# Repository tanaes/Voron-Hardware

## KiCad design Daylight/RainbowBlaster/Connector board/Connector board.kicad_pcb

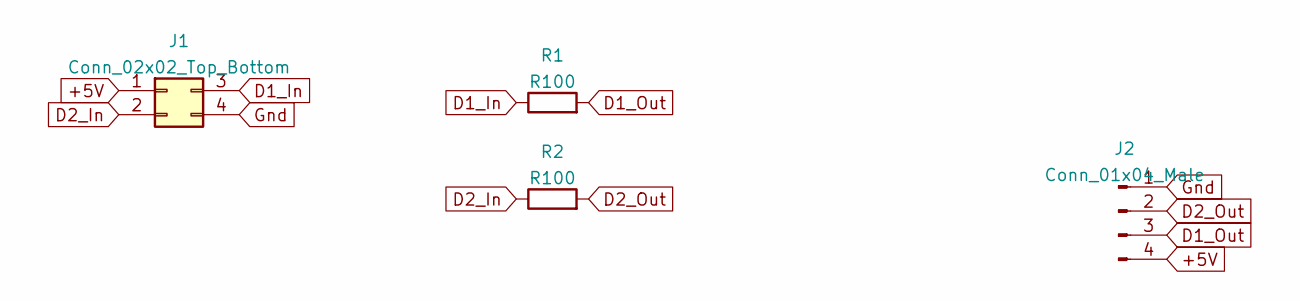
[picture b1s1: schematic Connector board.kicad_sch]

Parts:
J1: Conn_02x02_Top_Bottom; Molex_Micro-Fit_3.0_43045-0400_2x02_P3.00mm_Horizontal
J2: Conn_01x04_Male; PinHeader_1x04_P2.54mm_Vertical
R1, R2: R100; R_0805_2012Metric

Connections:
+5V: J1.1, J2.4
D1_In: J1.3, R1.1
D1_Out: J2.3, R1.2
D2_In: J1.2, R2.1
D2_Out: J2.2, R2.2
Gnd: J1.4, J2.1

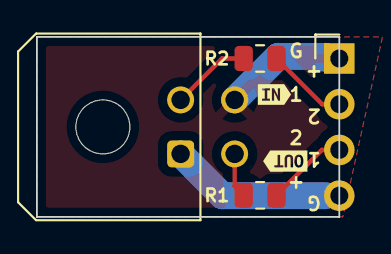
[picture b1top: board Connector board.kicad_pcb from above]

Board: 2 copper layers, 16.8 x 10.0 mm, 6 parts (0 on the bottom side), 6 nets.

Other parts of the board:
kibuzzard-6318DB81: G***; kibuzzard-6318DB81
kibuzzard-6318DBA2: G***; kibuzzard-6318DBA2

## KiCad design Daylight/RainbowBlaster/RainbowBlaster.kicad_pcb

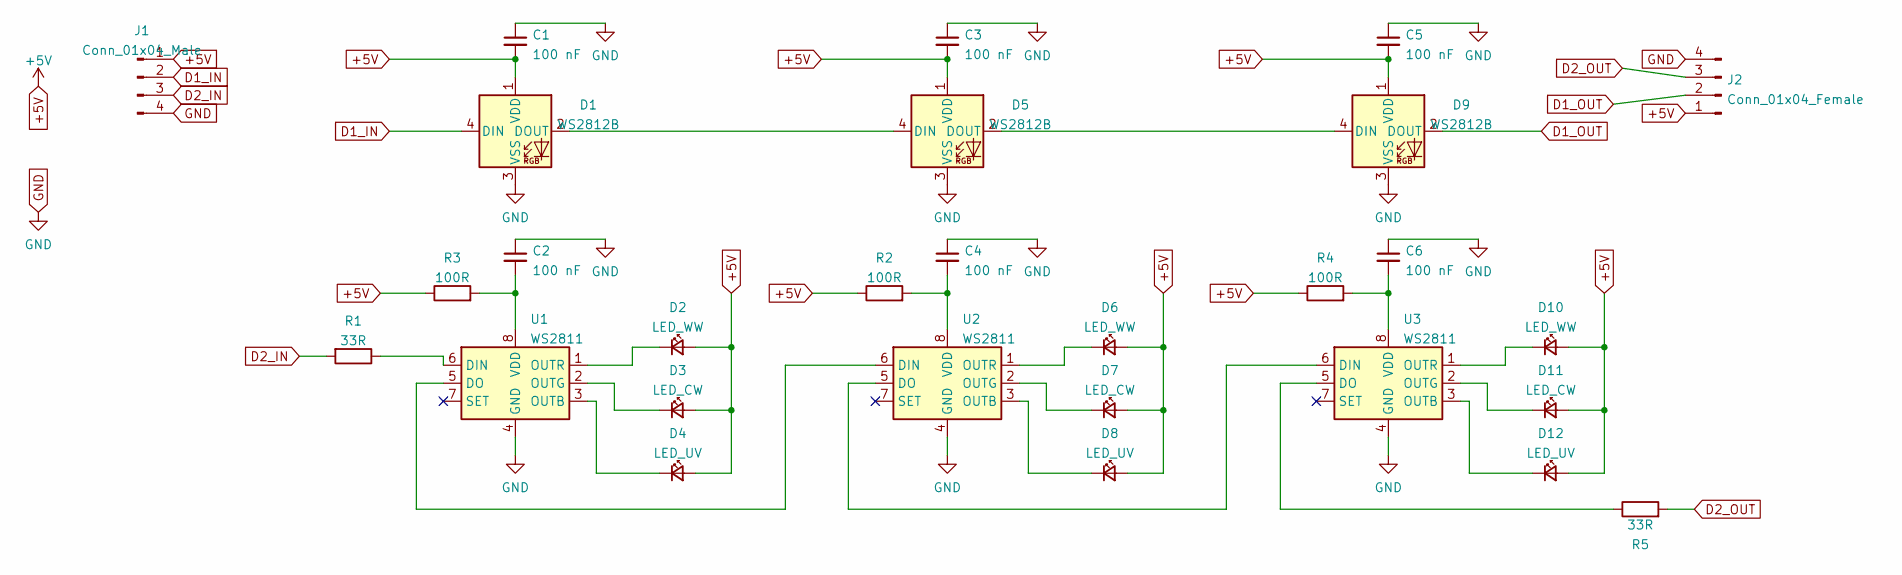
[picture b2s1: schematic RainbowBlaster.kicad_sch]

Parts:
C1, C2, C3, C4, C5, C6: 100 nF; C_0603_1608Metric
D1, D5, D9: WS2812B; LED_SK6812MINI_PLCC4_3.5x3.5mm_P1.75mm
D2, D6, D10: LED_WW; LED_PLCC_2835
D3, D7, D11: LED_CW; LED_PLCC_2835
D4, D8, D12: LED_UV; LED_PLCC_2835
J1: Conn_01x04_Male; PinHeader_1x04_P2.54mm_Vertical
J2: Conn_01x04_Female; PinHeader_1x04_P2.54mm_Vertical
R1, R5: 33R; R_0603_1608Metric
R2, R3, R4: 100R; R_0603_1608Metric
U1, U2, U3: WS2811; SO-8_3.9x4.9mm_P1.27mm

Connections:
+5V: C1.2, C3.2, C5.2, D1.1 (VDD), D2.2 (A), D3.2 (A), D4.2 (A), D5.1 (VDD), D6.2 (A), D7.2 (A), D8.2 (A), D9.1 (VDD), D10.2 (A), D11.2 (A), D12.2 (A), J1.1, J2.1, R2.1, R3.1, R4.1
D1_IN: D1.4 (DIN), J1.2
D1_OUT: D9.2 (DOUT), J2.2
D2_IN: J1.3, R1.2
D2_OUT: J2.3, R5.2
GND: C1.1, C2.1, C3.1, C4.1, C5.1, C6.1, D1.3 (VSS), D5.3 (VSS), D9.3 (VSS), J1.4, J2.4, U1.4 (GND), U2.4 (GND), U3.4 (GND)
unnamed: C2.2, R3.2, U1.8 (VDD)
unnamed: C4.2, R2.2, U2.8 (VDD)
unnamed: C6.2, R4.2, U3.8 (VDD)
unnamed: D1.2 (DOUT), D5.4 (DIN)
unnamed: D2.1 (K), U1.1 (OUTR)
unnamed: D3.1 (K), U1.2 (OUTG)
unnamed: D4.1 (K), U1.3 (OUTB)
unnamed: D5.2 (DOUT), D9.4 (DIN)
unnamed: D6.1 (K), U2.1 (OUTR)
unnamed: D7.1 (K), U2.2 (OUTG)
unnamed: D8.1 (K), U2.3 (OUTB)
unnamed: D10.1 (K), U3.1 (OUTR)
unnamed: D11.1 (K), U3.2 (OUTG)
unnamed: D12.1 (K), U3.3 (OUTB)
unnamed: R1.1, U1.6 (DIN)
unnamed: R5.1, U3.5 (DO)
unnamed: U1.5 (DO), U2.6 (DIN)
unnamed: U2.5 (DO), U3.6 (DIN)

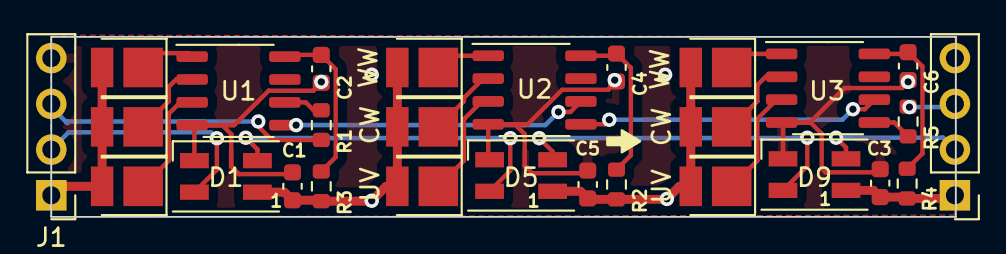
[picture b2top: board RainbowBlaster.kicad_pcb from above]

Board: 2 copper layers, 50.2 x 10.0 mm, 29 parts (1 on the bottom side), 24 nets.

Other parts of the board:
kibuzzard-6318CB10: G***; kibuzzard-6318CB10

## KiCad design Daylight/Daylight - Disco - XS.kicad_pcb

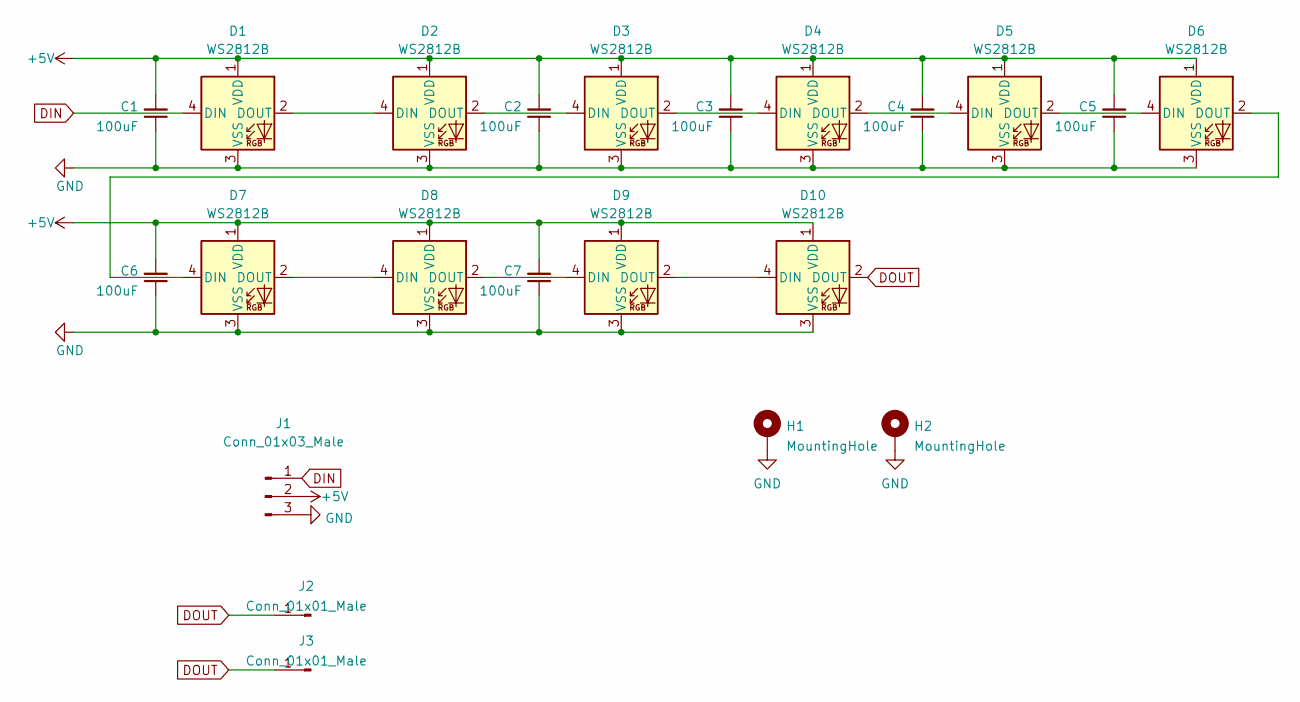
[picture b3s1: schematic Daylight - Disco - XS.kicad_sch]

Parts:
C1, C2, C3, C4, C5, C6, C7: 100uF; C_0805_2012Metric_Pad1.18x1.45mm_HandSolder
D1, D2, D3, D4, D5, D6, D7, D8, D9, D10: WS2812B; LED_WS2812B_PLCC4_5.0x5.0mm_P3.2mm
H1, H2: MountingHole; MountingHole_3.2mm_M3_Pad_Via
J1: Conn_01x03_Male; JST_XH_S3B-XH-A-1_1x03_P2.50mm_Horizontal
J2, J3: Conn_01x01_Male; PinHeader-1-with-SMDpad

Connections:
+5V: C1.2, C2.2, C3.2, C4.2, C5.2, C6.2, C7.2, D1.1 (VDD), D2.1 (VDD), D3.1 (VDD), D4.1 (VDD), D5.1 (VDD), D6.1 (VDD), D7.1 (VDD), D8.1 (VDD), D9.1 (VDD), D10.1 (VDD), J1.2
DIN: D1.4 (DIN), J1.1
DOUT: D10.2 (DOUT), J2.1, J3.1
GND: C1.1, C2.1, C3.1, C4.1, C5.1, C6.1, C7.1, D1.3 (VSS), D2.3 (VSS), D3.3 (VSS), D4.3 (VSS), D5.3 (VSS), D6.3 (VSS), D7.3 (VSS), D8.3 (VSS), D9.3 (VSS), D10.3 (VSS), H1.1, H2.1, J1.3
unnamed: D1.2 (DOUT), D2.4 (DIN)
unnamed: D2.2 (DOUT), D3.4 (DIN)
unnamed: D3.2 (DOUT), D4.4 (DIN)
unnamed: D4.2 (DOUT), D5.4 (DIN)
unnamed: D5.2 (DOUT), D6.4 (DIN)
unnamed: D6.2 (DOUT), D7.4 (DIN)
unnamed: D7.2 (DOUT), D8.4 (DIN)
unnamed: D8.2 (DOUT), D9.4 (DIN)
unnamed: D9.2 (DOUT), D10.4 (DIN)

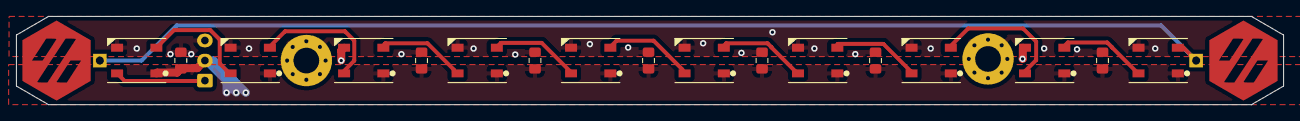
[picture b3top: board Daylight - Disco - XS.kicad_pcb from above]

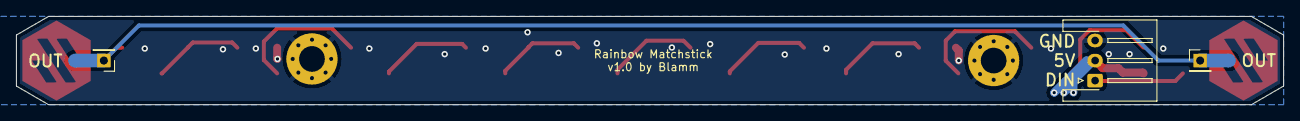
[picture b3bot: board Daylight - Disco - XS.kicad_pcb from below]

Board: 2 copper layers, 158.0 x 11.0 mm, 22 parts (3 on the bottom side), 13 nets.

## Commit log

2022-06-29 Add Daylight XS and Disco
2022-09-07 added rainbowblaster to Daylight
2022-09-07 assembly files
2022-09-07 added mono leds
